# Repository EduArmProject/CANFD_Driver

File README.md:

# EduArm – Daisy-Chained CAN-FD Stepper Motor Driver

Carte driver pour moteur pas à pas **NEMA 17**, pilotée en **CAN-FD** et **chaînable** (daisy-chain). Elle se fixe directement au dos du moteur et embarque un **encodeur magnétique 14 bits** pour connaître la position de l'arbre.

Conçue pour le projet **EduArm** (bras robotique éducatif).

| | |
|---|---|
| **Auteur** | Corentin_k_ |
| **Date** | 15/11/2026 |
| **Version** | V1  |
| **Outil** | KiCad 10.0.8 |

---

## Sommaire

1. [Structure du dépôt](#structure-du-dépôt)
2. [Fonctionnalités](#fonctionnalités)
3. [Aperçu](#aperçu)
4. [Architecture](#architecture)
5. [Caractéristiques](#caractéristiques)
6. [Composants principaux](#composants-principaux)
7. [Protections d'entrée](#protections-dentrée)
8. [Connecteurs et interface](#connecteurs-et-interface)
9. [Brochage du microcontrôleur](#brochage-du-microcontrôleur)

---
## Structure du dépôt

```
.
├── README.md
├── CANFD_DRIVER.kicad_pro
├── CANFD_DRIVER.kicad_sch
├── CANFD_DRIVER.kicad_pcb
├── lib/                  # symboles et empreintes et modèle 3D
└── docs/
    ├── CANFD_DRIVER_sch.pdf
    ├── CANFD_DRIVER_pcb.pdf
    └── img/
```

---

## Fonctionnalités

- Pilotage d'un moteur pas à pas NEMA 17 par un **TMC2209** : microstepping jusqu'à 1/256, courant réglable par UART, modes **StealthChop2** (silencieux) et **SpreadCycle**.
- **Détection de blocage sans capteur** (StallGuard4) : la broche `DIAG` passe à l'état haut au calage du moteur.
- Bus **CAN-FD** (jusqu'à 5 Mbit/s) avec **deux connecteurs XT30** qui transportent l'alimentation 24 V et le bus : les cartes se chaînent les unes aux autres.
- **Adresse CAN** réglable par un commutateur DIP (8 adresses) et **terminaison 120 Ω** activable.
- **Encodeur magnétique AS5047P** (14 bits, SPI) placé dans l'axe du moteur.
- Alimentation 24 V protégée (fusible + TVS), régulateur **3,3 V** intégré.
- Programmation et débogage par **SWD** (ST-Link), boutons `BOOT` et `RST`, 3 LED d'état.

## Aperçu

### Schématique

[Schématique complète (PDF)](./docs/CANFD_DRIVER_SCH.pdf)

### PCB

[(PDF)](docs/CANFD_DRIVER_PCB.pdf)

### Rendu 3D

---

## Architecture

```mermaid
flowchart TB
    PWR["Alimentation 24 V<br/>XT30 x2 (chaînage)"] --> FUSE["Fusible 3 A + TVS 26 V"]
    FUSE --> TMC["TMC2209<br/>driver pas à pas"]
    FUSE --> BUCK["Buck 3,3 V<br/>LMR50410"]
    BUCK -->|"3,3 V"| MCU["STM32G431CBT6"]
    MCU -->|"STEP / DIR / EN / UART"| TMC
    TMC -->|"DIAG"| MCU
    TMC -->|"2 phases"| MOT["Moteur NEMA 17"]
    MCU <-->|"SPI"| ENC["AS5047P<br/>encodeur 14 bits"]
    MCU <-->|"FDCAN1"| CANT["TCAN3413<br/>+ TVS DSM712"]
    CANT <--> BUS["Bus CAN-FD<br/>XT30 x2 (chaînage)"]
    SWD["Connecteur SWD<br/>ST-Link"] <--> MCU
```

---

## Caractéristiques

| Paramètre | Valeur |
|---|---|
| Tension d'alimentation | **24 V DC** nominal (limite du TMC2209 : 4,75 à 29 V) |
| Courant moteur | Réglable par UART, jusqu'à **1,77 A RMS** (limite matérielle : sense 2 × 0,11 Ω). **NEMA 17 jusqu'à 1,5 A** |
| Microstepping | Jusqu'à 1/256 |
| Bus de communication | CAN-FD, 5 Mbit/s maximum |
| Adresses CAN | 8 (DIP 3 bits) |
| Capteur de position | AS5047P, 14 bits (16 384 positions par tour) |
| Microcontrôleur | STM32G431CBT6 (Cortex-M4F, 128 Ko Flash, LQFP48) |
| Horloge | Quartz 16 MHz (HSE) |
| PCB | 4 couches, 1,6 mm, **42,3 × 42,3 mm**, entraxe de fixation **31 mm** (NEMA 17) |
| Règles de conception | Piste / espace min. 0,25 / 0,20 mm, perçage min. 0,3 mm |

---

## Composants principaux

> Prix indicatifs relevés sur LCSC (novembre 2026), susceptibles de varier.

### Microcontrôleur

**STM32G431CBT6** – Cortex-M4F avec FDCAN, LQFP48.
[LCSC C529355](https://www.lcsc.com/product-detail/C529355.html) – 4,43 € l'unité

**Quartz X322516MLB4SI** – 16 MHz, 9 pF, boîtier 3225, pour l'horloge HSE.
[LCSC C13738](https://www.lcsc.com/product-detail/C13738.html) – 0,45 € les 5

### Driver de moteur pas à pas

**TMC2209-LA-T** (Trinamic / Analog Devices)
[LCSC C2150710](https://www.lcsc.com/product-detail/C2150710.html) – 2,57 € l'unité

| | |
|---|---|
| Tension moteur | 4,75 à 29 V |
| Courant de sortie | jusqu'à 2 A RMS |
| Interfaces | STEP / DIR et UART (adresse 0) |
| Microstepping | 1/8 à 1/64 par broches, jusqu'à 1/256 par UART |
| Modes | StealthChop2 (silencieux), SpreadCycle (couple élevé), StallGuard4 (détection de blocage) |
| Mise en veille | Broche `EN` tirée à 3,3 V par une résistance : **moteur désactivé au démarrage** |

### Alimentation 3,3 V

**LMR50410Y3FQDBVRQ1** – régulateur buck synchrone 3,3 V fixe, 2,1 MHz.
[LCSC C5219374](https://www.lcsc.com/product-detail/C5219374.html) – 1,46 € l'unité

| | |
|---|---|
| Entrée | 4 à 36 V |
| Sortie | 3,3 V, 1 A (alimente MCU, CAN, encodeur) |

La source du 3,3 V se choisit avec le jumper à souder `JP1` : position 1-2 pour alimenter la carte par le ST-Link, position 2-3 pour l'alimenter par le buck.

### Encodeur magnétique

**AS5047P-ATSM** – capteur de position angulaire 14 bits, sortie SPI.
[LCSC C962063](https://www.lcsc.com/product-detail/C962063.html) – 4,81 € l'unité

| | |
|---|---|
| Résolution | 14 bits |
| Alimentation | 3,3 V, environ 15 mA |
| Interface | SPI (mode 1) |

### Transceiver CAN-FD

**TCAN3413DR** – transceiver CAN-FD 3,3 V.
[LCSC C22433320](https://www.lcsc.com/product-detail/C22433320.html) – 1 € l'unité

| | |
|---|---|
| Débit | jusqu'à 5 Mbit/s |
| Courant d'alimentation | environ 42 mA |
| Entrées logiques | TXD / RXD à 3,3 V (FDCAN1 du STM32) |
| Sorties bus | CANH / CANL |

**DSM712** (réseau TVS double) – protection ESD des lignes CANH / CANL.
[LCSC C502564](https://www.lcsc.com/product-detail/C502564.html) – 1,27 € les 20

### Interface utilisateur

| Fonction | Référence | LCSC | Prix |
|---|---|---|---|
| DIP 4 positions | 3 bits d'adresse CAN + 1 terminaison | [C54769760](https://www.lcsc.com/product-detail/C54769760.html) | 0,54 € l'unité |
| LED rouge | Présence du 3,3 V | [C965812](https://www.lcsc.com/product-detail/C965812.html) | 0,66 € les 100 |
| LED verte | Initialisation réussie | [C965815](https://www.lcsc.com/product-detail/C965815.html) | 0,62 € les 100 |
| LED bleue | Transmission CAN en cours | [C965817](https://www.lcsc.com/product-detail/C965817.html) | 0,72 € les 100 |
| Boutons | `BOOT` et `RST` | [C720477](https://www.lcsc.com/product-detail/C720477.html) | 0,48 € les 10 |

---

## Protections d'entrée

L'alimentation 24 V traverse deux protections avant d'atteindre le driver et le régulateur.

| Composant | Référence | Rôle |
|---|---|---|
| **Fusible F1** | SART S1206-SD-3.0A, 3 A temporisé, 63 V DC, pouvoir de coupure 50 A. [LCSC C845163](https://www.lcsc.com/product-detail/C845163.html) – 0,35 € les 5 | Coupe le circuit en cas de court-circuit ou de surintensité prolongée (driver en défaut, par exemple).   |
| **TVS1** | SMAJ26A, tension de service 26 V. [LCSC C908774](https://www.lcsc.com/product-detail/C908774.html) – 0,54 € les 20 | Absorbe les surtensions transitoires (pics de régénération du moteur, commutations). Protège le TMC2209 (maximum absolu 32 V) et le buck. |

> **Pas de protection contre l'inversion de polarité** : les connecteurs XT30 sont détrompés. Bien faire attention au cablage avant le premier branchement !

---

## Connecteurs et interface

### Alimentation et bus CAN (J1, J2)

Deux connecteurs **XT30PW (2+2)** montés en parallèle pour le chaînage. Chacun transporte l'alimentation 24 V (broches P et N) et le bus CAN (broches de signal S1 et S2).
[C19268030](https://www.lcsc.com/product-detail/C19268030.html) + [C19268028](https://www.lcsc.com/product-detail/C19268028.html) – 0,57 € + 0,35 € l'unité

| Broche | Signal |
|---|---|
| P | +24 V |
| N | GND |
| S1 | CAN_H |
| S2 | CAN_L |

### Sortie moteur (J5)

Connecteur 4 broches. [C160349](https://www.lcsc.com/product-detail/C160349.html), [C160356](https://www.lcsc.com/product-detail/C160356.html), [C157898](https://www.lcsc.com/product-detail/C157898.html) – 2,43 € les 100 + 1,09 € les 5 + 0,45 € les 10

| Broche | Signal | Bobine |
|:---:|---|---|
| 1 | OA1 | A |
| 2 | OA2 | A |
| 3 | OB1 | B |
| 4 | OB2 | B |

### Programmation (SWD)

| Broche | Signal |
|:---:|---|
| 1 | GND |
| 2 | V_STLINK |
| 3 | SWDIO |
| 4 | SWCLK |
| 5 | SWNRST |

### Commutateur DIP

| Interrupteur | Fonction |
|:---:|---|
| 1 à 3 | Adresse CAN (0 à 7) |
| 4 | Terminaison CAN 120 Ω (à fermer sur la dernière carte du bus) |

---

## Brochage du microcontrôleur

| Broche | Signal | Fonction |
|:---:|---|---|
| PA8 | `MOTOR_EN` | Activation du driver (actif à l'état bas) |
| PA9 | `MOTOR_STEP` | Impulsions de pas (TIM1) |
| PB15 | `MOTOR_DIR` | Sens de rotation |
| PB10 | `MOTOR_UART` | UART du TMC2209 (USART3, mode half-duplex) |
| PB14 | `MOTOR_DIAG` | Sortie StallGuard / erreur du driver |
| PA5 / PA6 / PA7 | `SPI_CLK` / `SPI_MISO` / `SPI_MOSI` | SPI1 vers l'encodeur |
| PA1 | `SPI_CS` | Chip select de l'encodeur |
| PA11 / PA12 | `CAN_RX` / `CAN_TX` | FDCAN1 |
| PB4 / PA15 / PB12 | `DIP1` / `DIP2` / `DIP3` | Adresse CAN |
| PB11 | `LED_BLUE` | Transmission CAN |
| PB13 | `LED_GREEN` | Initialisation |
| PA13 / PA14 | `SWDIO` / `SWCLK` | Débogage |
| PB8 | `BOOT0` | Bouton `BOOT` |
| PG10 | `NRST` | Bouton `RST` |

---

*Corentin K. – Projet EduArm – 2026*

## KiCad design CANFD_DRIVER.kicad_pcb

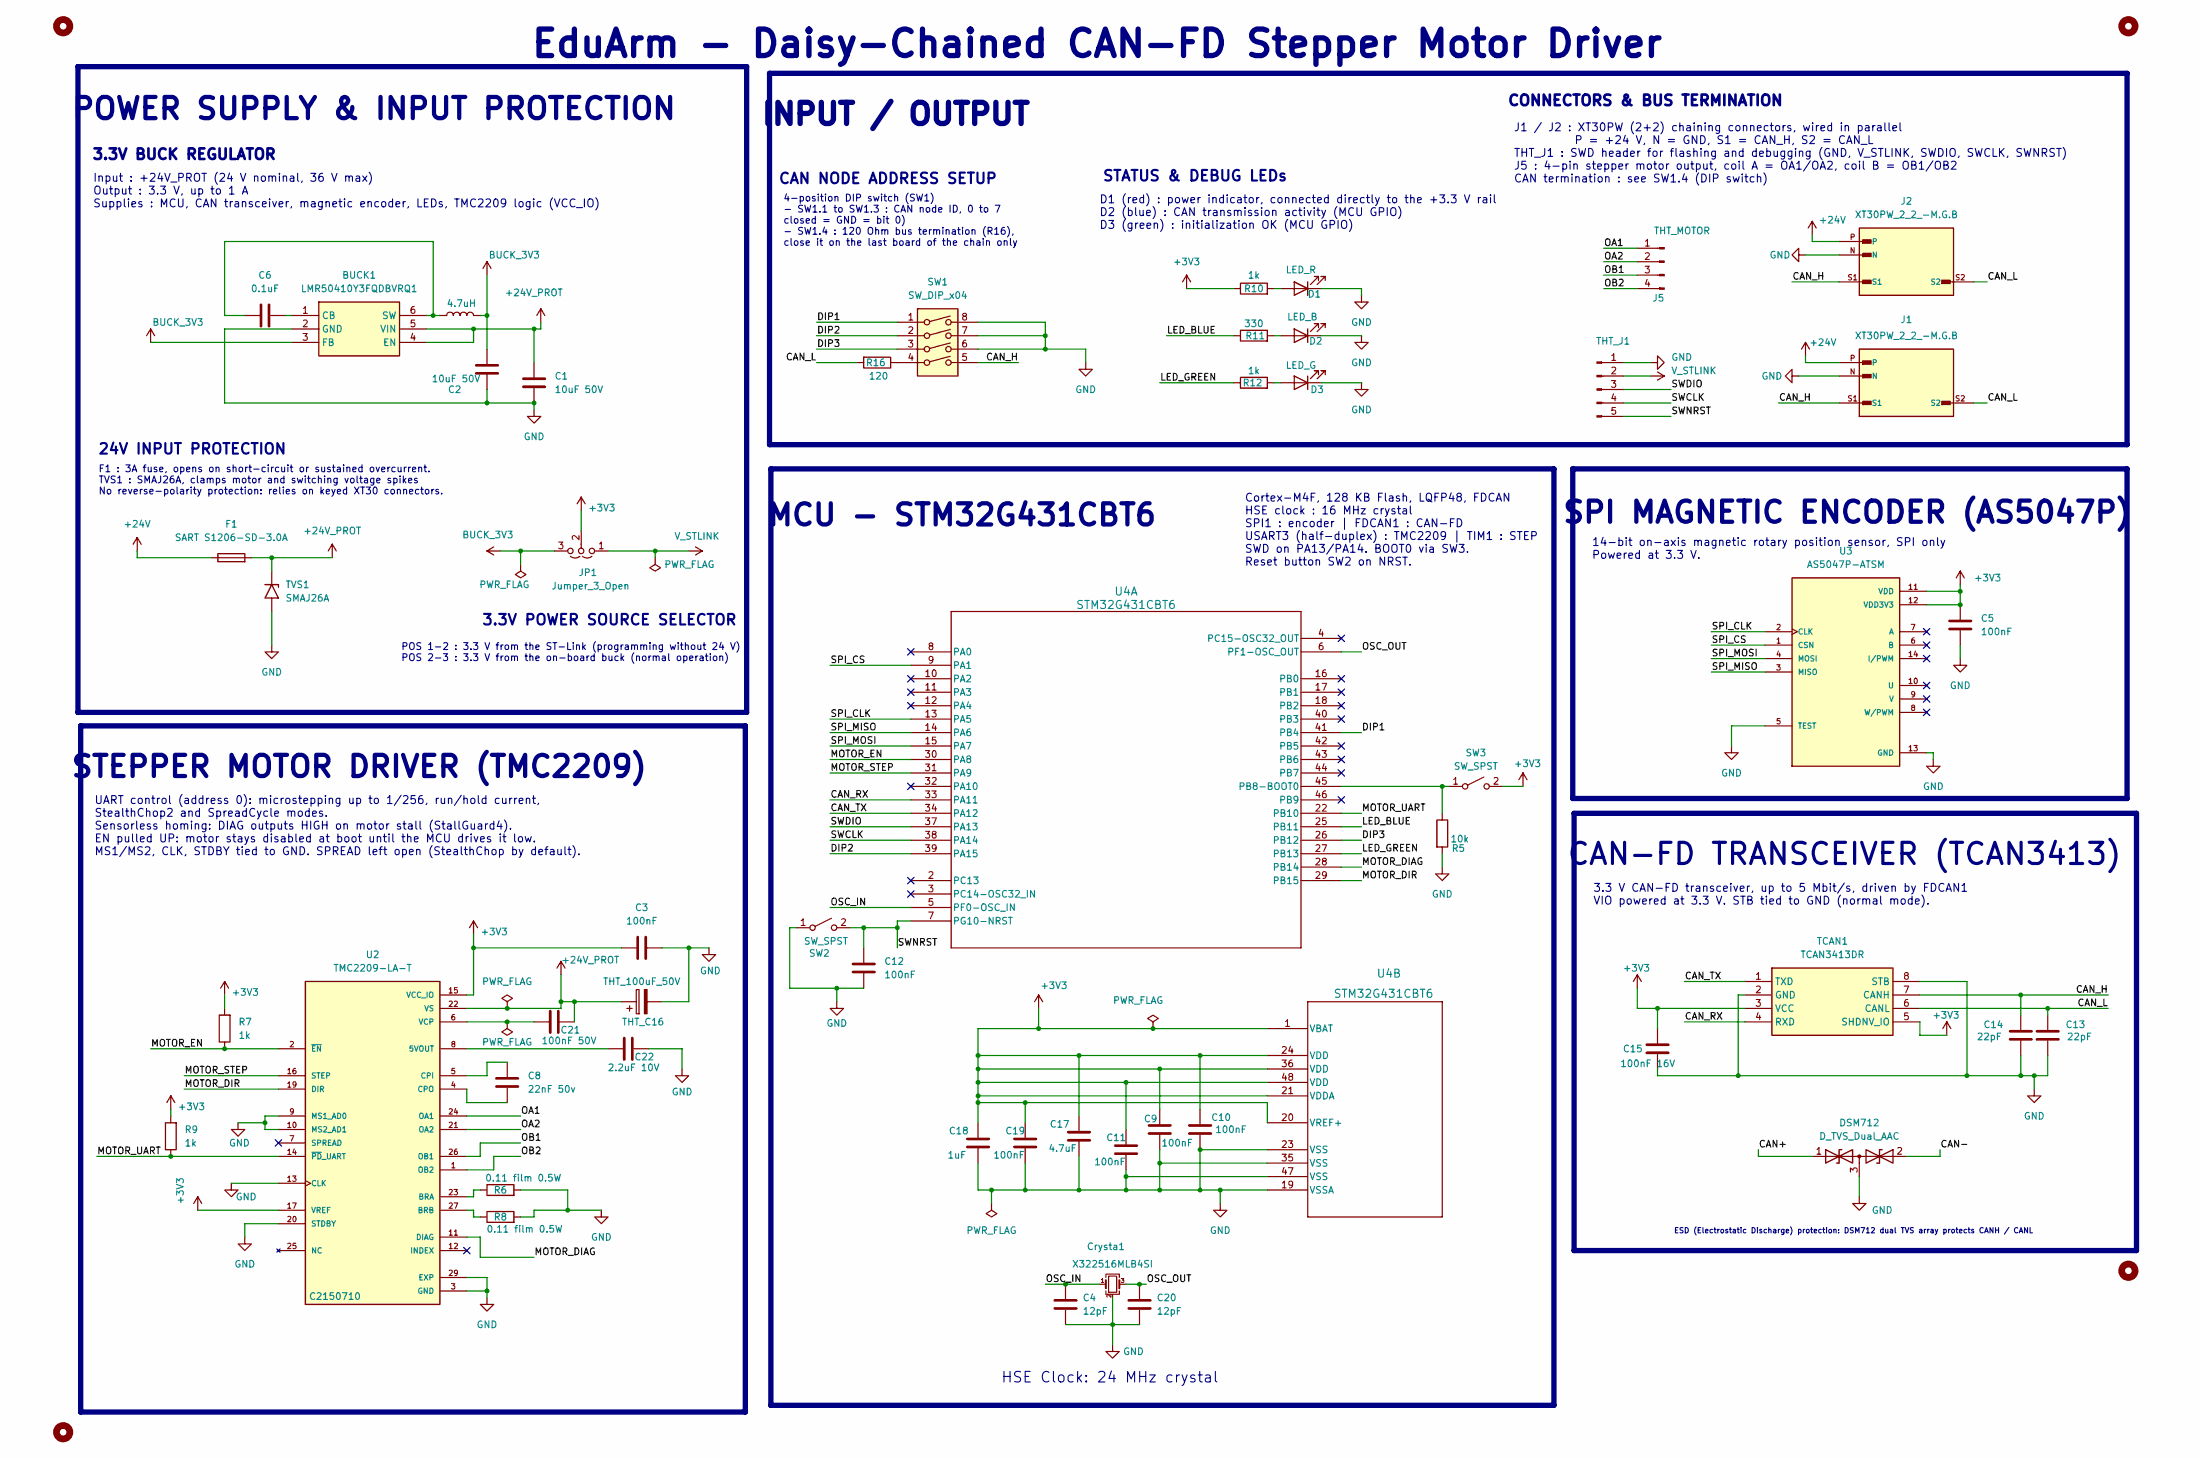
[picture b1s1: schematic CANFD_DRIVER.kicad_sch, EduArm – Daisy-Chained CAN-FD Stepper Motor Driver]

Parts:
BUCK1: LMR50410Y3FQDBVRQ1; SOT95P280X145-6N; Manufacturer_Part_Number LMR50410Y3FQDBVRQ1; Mouser Part Number 595-R50410Y3FQDBVRQ1
C1, C2: 10uF 50V; C_0805_2012Metric
C3, C5, C9, C10, C11, C12, C19: 100nF; C_0603_1608Metric
C4, C20: 12pF; C_0603_1608Metric
C6: 0.1uF; C_0603_1608Metric
C8: 22nF 50v; C_0603_1608Metric
C13, C14: 22pF; C_0603_1608Metric
C15: 100nF 16V; C_0603_1608Metric
C17: 4.7uF; C_0603_1608Metric
C18: 1uF; C_0603_1608Metric
C21: 100nF 50V; C_0603_1608Metric
C22: 2.2uF 10V; C_0603_1608Metric
Crysta1: X322516MLB4SI; Crystal_SMD_3225-4Pin_3.2x2.5mm; LCSC C13738
D1: LED_R; LED_0805_2012Metric; LCSC C2286
D2: LED_B; LED_0805_2012Metric; LCSC C2288
D3: LED_G; LED_0805_2012Metric; LCSC C72043
DSM712: D_TVS_Dual_AAC; SOT-23; LCSC C32677
F1: SART S1206-SD-3.0A; Fuse_1206_3216Metric; LCSC C553935
H1, H2, H3, H4: MountingHole; MountingHole_3.2mm_M3
J1, J2: XT30PW_2_2_-M.G.B; AMASS_XT30PW_2_2_-M.G.B; MPN XT30PW(2+2)-M.G.B
J5: THT_MOTOR; JST_PH_S4B-PH-K_1x04_P2.00mm_Horizontal
JP1: Jumper_3_Open; PinHeader_1x03_P2.54mm_Vertical
L1: 4.7uH; L_Taiyo-Yuden_NR-40xx
R5: 10k; R_0603_1608Metric
R6, R8: 0.11 film 0.5W; R_1206_3216Metric
R7, R9, R10, R12: 1k; R_0603_1608Metric
R11: 330; R_0603_1608Metric
R16: 120; R_0603_1608Metric
SW1: SW_DIP_x04; SW_DIP_SPSTx04_Slide_Copal_CHS-04A_W5.08mm_P1.27mm_JPin
SW2, SW3: SW_SPST; SW_SPST_B3U-1000P
TCAN1: TCAN3413DR; SOIC127P600X175-8N; Manufacturer_Part_Number TCAN3413DR; Mouser Part Number 595-TCAN3413DR
THT_C16: THT_100uF_50V; CP_Radial_D6.3mm_P2.50mm
THT_J1: Conn_01x05_Pin; PinHeader_1x05_P2.54mm_Vertical
TVS1: SMAJ26A; D_SMA; LCSC C383018
U2: TMC2209-LA-T; QFN50P500X500X90-29N; PARTREV 1.09; LCSC C2150710
U3: AS5047P-ATSM; SOP65P640X120-14N; PARTREV 1-01; LCSC C962063
U4: STM32G431CBT6; LQFP48-7x7mm

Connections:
+3V3: C3.1, C5.1, C9.1, C10.1, C11.1, C15.1, C17.1, C18.1, C19.1, JP1.2 (C), R7.2, R9.2, R10.1, SW3.2 (B), TCAN1.3 (VCC), TCAN1.5 (SHDNV_IO), U2.15 (VCC_IO), U2.17 (VREF), U3.11 (VDD), U3.12 (VDD3V3), U4.1 (VBAT), U4.20 (VREF+), U4.21 (VDDA), U4.24 (VDD), U4.36 (VDD), U4.48 (VDD)
+24V: F1.1, J1.P, J2.P
+24V_PROT: BUCK1.4 (EN), BUCK1.5 (VIN), C1.1, C21.2, F1.2, THT_C16.1, TVS1.1 (A1), U2.22 (VS), U2.28 (VS)
/CAN_RX: TCAN1.4 (RXD), U4.33 (PA11)
/CAN_TX: TCAN1.1 (TXD), U4.34 (PA12)
/DIP1: SW1.1, U4.41 (PB4)
/DIP2: SW1.2, U4.39 (PA15)
/DIP3: SW1.3, U4.26 (PB12)
/LED_BLUE: R11.1, U4.25 (PB11)
/LED_GREEN: R12.1, U4.27 (PB13)
/MOTOR_DIAG: U2.11 (DIAG), U4.28 (PB14)
/MOTOR_DIR: U2.19 (DIR), U4.29 (PB15)
/MOTOR_EN: R7.1, U2.2 (~EN), U4.30 (PA8)
/MOTOR_STEP: U2.16 (STEP), U4.31 (PA9)
/MOTOR_UART: R9.1, U2.14 (~PD_UART), U4.22 (PB10)
/OA1: J5.1, U2.24 (OA1)
/OA2: J5.2, U2.21 (OA2)
/OB1: J5.3, U2.26 (OB1)
/OB2: J5.4, U2.1 (OB2)
/OSC_IN: C4.1, Crysta1.1, U4.5 (PF0-OSC_IN)
/OSC_OUT: C20.1, Crysta1.3, U4.6 (PF1-OSC_OUT)
/SPI_CLK: U3.2 (CLK), U4.13 (PA5)
/SPI_CS: U3.1 (CSN), U4.9 (PA1)
/SPI_MISO: U3.3 (MISO), U4.14 (PA6)
/SPI_MOSI: U3.4 (MOSI), U4.15 (PA7)
/SWCLK: THT_J1.4, U4.38 (PA14)
/SWDIO: THT_J1.3, U4.37 (PA13)
/SWNRST: C12.1, SW2.2 (B), THT_J1.5, U4.7 (PG10-NRST)
BUCK_3V3: BUCK1.3 (FB), C2.2, JP1.3 (B), L1.2
GND: BUCK1.2 (GND), C1.2, C2.1, C3.2, C4.2, C5.2, C9.2, C10.2, C11.2, C12.2, C13.2, C14.2, C15.2, C17.2, C18.2, C19.2, C20.2, C22.2, Crysta1.2 (G), Crysta1.4 (G), D1.1 (K), D2.1 (K), D3.1 (K), DSM712.3 (common), J1.N, J2.N, R5.2, R6.2, R8.2, SW1.6, SW1.7, SW1.8, SW2.1 (A), TCAN1.2 (GND), TCAN1.8 (STB), THT_C16.2, THT_J1.1, TVS1.2 (A2), U2.3 (GND), U2.9 (MS1_AD0), U2.10 (MS2_AD1), U2.13 (CLK), U2.18 (GND), U2.20 (STDBY), U2.29 (EXP), U3.5 (TEST), U3.13 (GND), U4.19 (VSSA), U4.23 (VSS), U4.35 (VSS), U4.47 (VSS)
unnamed: BUCK1.1 (CB), C6.2
unnamed: BUCK1.6 (SW), C6.1, L1.1
unnamed: D1.2 (A), R10.2
unnamed: D2.2 (A), R11.2
unnamed: D3.2 (A), R12.2
unnamed: R16.1, SW1.4
unnamed: R5.1, SW3.1 (A), U4.45 (PB8-BOOT0)
unnamed: C22.1, U2.8 (5VOUT)
unnamed: R6.1, U2.23 (BRA)
unnamed: R8.1, U2.27 (BRB)
unnamed: C8.1, U2.5 (CPI)
unnamed: C8.2, U2.4 (CPO)
unnamed: C21.1, U2.6 (VCP)
V_STLINK: JP1.1 (A), THT_J1.2

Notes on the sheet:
INPUT / OUTPUT
3.3V POWER SOURCE SELECTOR
POWER SUPPLY & INPUT PROTECTION
ESD (Electrostatic Discharge) protection: DSM712 dual TVS array protects CANH / CANL
STATUS & DEBUG LEDs
CONNECTORS & BUS TERMINATION
CAN-FD TRANSCEIVER (TCAN3413)
Input : +24V_PROT (24 V nominal, 36 V max) Output : 3.3 V, up to 1 A Supplies : MCU, CAN transceiver, magnetic encoder, LEDs, TMC2209 logic (VCC_IO)
POS 1-2 : 3.3 V from the ST-Link (programming without 24 V) POS 2-3 : 3.3 V from the on-board buck (normal operation)
MCU - STM32G431CBT6
F1 : 3A fuse, opens on short-circuit or sustained overcurrent. TVS1 : SMAJ26A, clamps motor and switching voltage spikes No reverse-polarity protection: relies on keyed XT30 connectors.
SPI MAGNETIC ENCODER (AS5047P)
J1 / J2 : XT30PW (2+2) chaining connectors, wired in parallel P = +24 V, N = GND, S1 = CAN_H, S2 = CAN_L THT_J1 : SWD header for flashing and debugging (GND, V_STLINK, SWDIO, SWCLK, SWNRST) J5 : 4-pin stepper motor output, coil A = OA1/OA2, coil B = OB1/OB2 CAN termination : see SW1.4 (DIP switch)
3.3 V CAN-FD transceiver, up to 5 Mbit/s, driven by FDCAN1 VIO powered at 3.3 V. STB tied to GND (normal mode).
14-bit on-axis magnetic rotary position sensor, SPI only Powered at 3.3 V.
4-position DIP switch (SW1) - SW1.1 to SW1.3 : CAN node ID, 0 to 7 closed = GND = bit 0) - SW1.4 : 120 Ohm bus termination (R16), close it on the last board of the chain only
CAN NODE ADDRESS SETUP
STEPPER MOTOR DRIVER (TMC2209)
24V INPUT PROTECTION
3.3V BUCK REGULATOR
HSE Clock: 24 MHz crystal
UART control (address 0): microstepping up to 1/256, run/hold current, StealthChop2 and SpreadCycle modes. Sensorless homing: DIAG outputs HIGH on motor stall (StallGuard4). EN pulled UP: motor stays disabled at boot until the MCU drives it low. MS1/MS2, CLK, STDBY tied to GND. SPREAD left open (St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
Cortex-M4F, 128 KB Flash, LQFP48, FDCAN HSE clock : 16 MHz crystal SPI1 : encoder | FDCAN1 : CAN-FD USART3 (half-duplex) : TMC2209 | TIM1 : STEP SWD on PA13/PA14. BOOT0 via SW3. Reset button SW2 on NRST.
D1 (red) : power indicator, connected directly to the +3.3 V rail D2 (blue) : CAN transmission activity (MCU GPIO) D3 (green) : initialization OK (MCU GPIO)
EduArm - Daisy-Chained CAN-FD Stepper Motor Driver

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
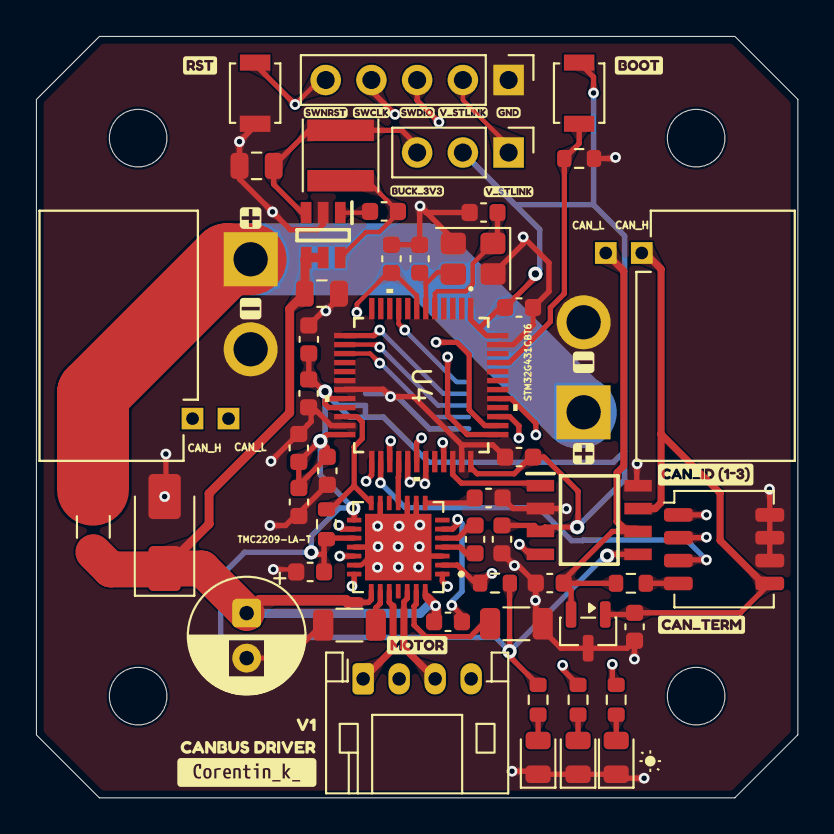
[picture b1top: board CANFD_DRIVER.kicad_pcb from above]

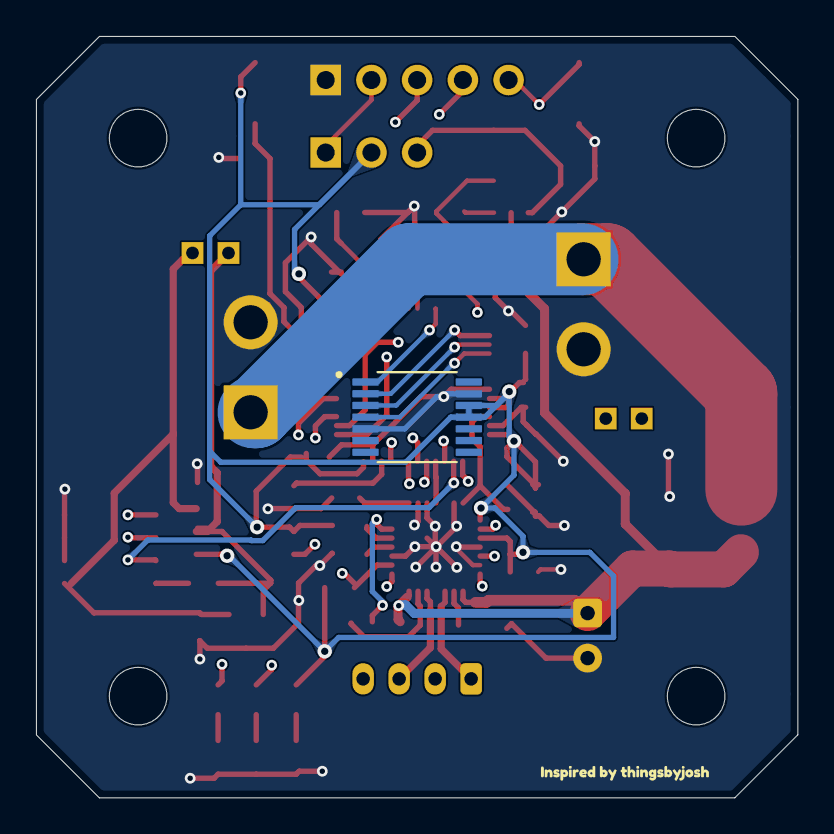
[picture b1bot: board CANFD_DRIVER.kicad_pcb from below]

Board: 4 copper layers, 42.3 x 42.3 mm, 79 parts (2 on the bottom side), 46 nets.

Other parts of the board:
H1#2, H2#2, H3#2, H4#2: MountingHole; MountingHole_3.2mm_M3
kobee-studio-0ff901aa3749: Kobee Studio; kobee-studio-9b8d820f1491
kobee-studio-1c92fabe67ea, kobee-studio-2f9d7cb4f695, kobee-studio-2350ff364bed, kobee-studio-274907c77ad6: Kobee Studio; kobee-studio-df525f03bb18
kobee-studio-5caaccfa7bba: Kobee Studio; kobee-studio-5caaccfa7bba
kobee-studio-6AF35F84, kobee-studio-6AF35FBE: Kobee Studio; kobee-studio-6AF35E75
kobee-studio-6AF35F98, kobee-studio-6AF35FAA: Kobee Studio; kobee-studio-6AF35F0A
kobee-studio-6c878dc4b8ed, kobee-studio-9f2ea64a79c8, kobee-studio-4183f564a4d6, kobee-studio-5765457420aa: Kobee Studio; kobee-studio-22fa00506c9f
kobee-studio-77491de6867f: Kobee Studio; kobee-studio-6AF35DA2
kobee-studio-c9fa37acf61b: Kobee Studio; kobee-studio-c9fa37acf61b
kobee-studio-c340ddf16d2c: Kobee Studio; kobee-studio-df525f03bb18
kobee-studio-d0747335aaa1: Kobee Studio; kobee-studio-df525f03bb18
kobee-studio-f8cb951f3cc0: Kobee Studio; kobee-studio-df525f03bb18
kobee-studio-f996f450d4d6: Kobee Studio; kobee-studio-22fa00506c9f
